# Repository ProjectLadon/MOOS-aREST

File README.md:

# MOOS-paREST
A connector between MOOS and aREST running on Arduino satellite nodes. It provides a direct linkage between aREST endpoints and MOOS variables.

## Dependencies
* MOOS-IvP
* https://github.com/Tencent/rapidjson/ -- provides JSON parse/deparse
* https://curl.haxx.se/libcurl/ -- provides HTTP client interface

## Configuration Options
* interface -- defines the aRest interface to be used, according to the following schema:
```
{
	"$schema": "http://json-schema.org/schema#",
	"id": "AREST_interface",
	"type": "object",
	"properties":{
		"oneOf": [
			{
				"type":"object",
				"properties": {
					"interfaceType": "serial",
					"interface": {
						"type":"string",
						"pattern": "",
						"$comment": "pattern needs to be filled in so it only accepts device names"
					},
					"speed": {"type":"integer", "$comment":"defaults to 115200"},
					"serialFormat": {
						"type":"string",
						"pattern": "",
						"$comment":"Pattern needs to be filled in so it only permits sane values",
						"$comment":"Defaults to 8N1"
					}
				},
				"required":["interfaceType", "interface"],
				"$comment": "This is for a serial interface"
			},
			{
				"type":"object",
				"properties": {
					"interfaceType": "network",
					"url": {"type":"string", "format": "uri"},
				},
				"required":["interfaceType", "url"],
				"$comment": "This is for a network interface"
			}
		]
	}
}
```
* digitalRead -- read a given digital pin and publish the result on MOOSDB as a BINARY, as defined by the following JSON schema:
```
{
	"$schema": "http://json-schema.org/schema#",
	"id": "AREST_digitalRead",
	"type": "object",
	"properties":{
		"function":"digitalRead",
		"pin":{"type":"number"},
		"variable":{
			"type":"string",
			"$comment": "This must be a free variable name; it will be published as a BINARY"
		}
	},
	"required":["function","pin","variable"]
}
```
* digitalWrite -- write from a given MOOSDB BINARY variable to a given digital pin, as defined by the following JSON schema:
```
{
	"$schema": "http://json-schema.org/schema#",
	"id": "AREST_digitalWrite",
	"type": "object",
	"properties":{
		"function":"digitalWrite",
		"pin":{"type":"number"},
		"variable":{
			"type":"string",
			"$comment": "This must be an existing BINARY variable"
		}
	},
	"required":["function","pin","variable"]
}
```
* analogRead -- read a given analog pin and publish the result on MOOSDB as a DOUBLE, as defined by the following JSON schema. Note that the offset value (if present) will be added to the received value and the result will be multiplied by the gain (if present) prior to publication.
```
{
	"$schema": "http://json-schema.org/schema#",
	"id": "AREST_analogRead",
	"type": "object",
	"properties":{
		"function":"analogRead",
		"pin":{"type":"number"},
		"variable":{
			"type":"string",
			"$comment": "This must be a free variable name; it will be published as a DOUBLE"
		},
		"offset":{"type":"integer"},
		"gain":{"type":"number"}
	},
	"required":["function","pin","variable"]
}
```
* analogWrite -- write from a given MOOSDB DOUBLE variable to a given analog pin, as defined by the following JSON schema. Note that the offset value (if present) will be added to the received value and the result will be multiplied by the gain (if present) prior to transmission.
```
{
	"$schema": "http://json-schema.org/schema#",
	"id": "AREST_analogWrite",
	"type": "object",
	"properties":{
		"function":"analogWrite",
		"pin":{"type":"number"},
		"variable":{
			"type":"string",
			"$comment": "This must be an existing DOUBLE variable"
		},
		"offset":{"type":"integer"},
		"gain":{"type":"number"},
		"maxValue":{"type":"integer"},
		"minValue":{"type":"integer"}
	},
	"required":["function","pin","variable"]
}
```
* variable -- read a given variable and publish the result on MOOSDB as a DOUBLE or STRING, as defined by the following JSON schema:
```
{
	"$schema": "http://json-schema.org/schema#",
	"id": "AREST_variable",
	"type": "object",
	"properties":{
		"function":"variable",
		"name":{"type":"string"},
		"variableType":{"type":"string","enum":["STRING","DOUBLE"]},
		"variable":{
			"type":"string",
			"$comment": "This must be a free variable name; it will be published as defined by variableType"
		}
	},
	"required":["function","name","variable","variableType"]
}
```
* function -- activate a given function with (optional) parameters and return the result on a MOOSDB variable. The behavior is defined by JSON with the following schema:
```
{
	"$schema": "http://json-schema.org/schema#",
	"id": "AREST_function",
	"type": "object",
	"properties":{
		"function":"function",
		"name":{"type":"string"},
		"parameters":{
			"type":"array",
			"items":{
				"type": "object",
				"properties": {
					"name": {"type":"string"},
					"inputVariable": {"type":"string"},
					"inputVariableType": {"type": "string", "enum":["DOUBLE", "STRING", "BINARY"]}
				},
				"required":["name", "inputVariable", "inputVariableType"]
			}
		},
		"returnType":{"type":"string","enum":["STRING","DOUBLE"]},
		"returnVariable":{
			"type":"string",
			"$comment": "This must be a free variable name; it will be published as a DOUBLE"
		}
	},
	"required":["function","name"]
}
```
* confFile -- path to a configuration file with any combination of other objects. The contents of the file must be a single JSON array of objects conforming to one or more of the previous schemas.
* digitalPollPeriod -- polling period for digitalRead items, in ticks.
* analogPollPeriod -- polling period for analogRead items, in ticks.
* functionPollPeriod -- polling period for function items, in ticks.
* variablePollPeriod -- polling period for variable items, in ticks.

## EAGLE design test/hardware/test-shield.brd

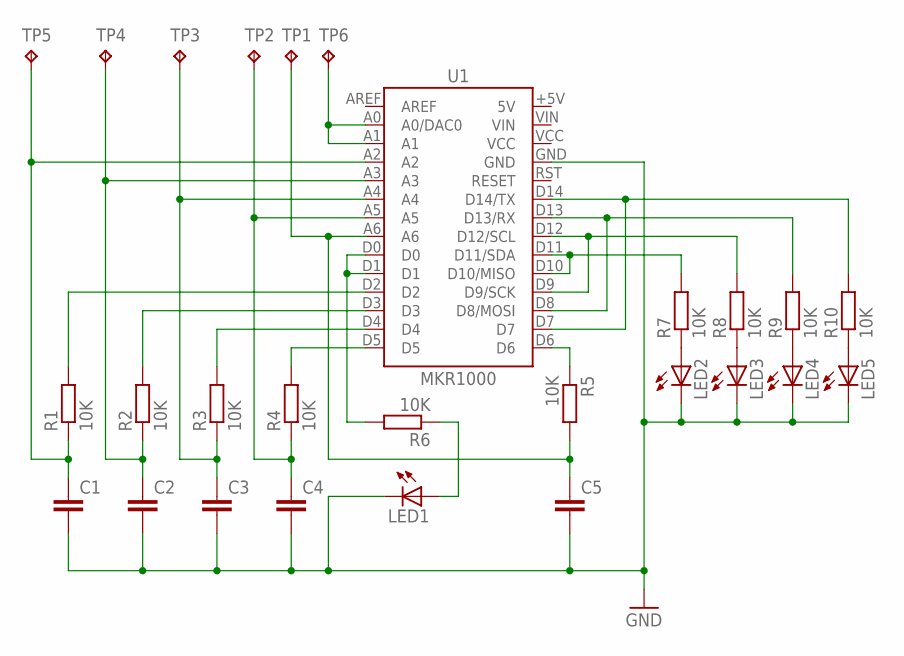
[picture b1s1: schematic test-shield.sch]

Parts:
C1, C2, C3, C4, C5: C-EUC0603; C0603
LED1, LED2, LED3, LED4, LED5: LEDCHIPLED_0805; CHIPLED_0805
R1, R2, R3, R4, R5, R6, R7, R8, R9, R10: 10K; R0603
TP1, TP2, TP3, TP4, TP5, TP6: TPPAD1-13; P1-13
U1: MKR1000; MKR1000-THRU-HOLE

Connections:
GND: C1.2, C2.2, C3.2, C4.2, C5.2, LED1.C, LED2.C, LED3.C, LED4.C, LED5.C, U1.GND
unnamed: R1.2, U1.D2
unnamed: R2.2, U1.D3
unnamed: R3.2, U1.D4
unnamed: R4.2, U1.D5
unnamed: R5.1, U1.D6
unnamed: C1.1, R1.1, TP5.TP, U1.A2
unnamed: C2.1, R2.1, TP4.TP, U1.A3
unnamed: C3.1, R3.1, TP3.TP, U1.A4
unnamed: C4.1, R4.1, TP2.TP, U1.A5
unnamed: R10.2, U1.D7, U1.D14 (D14/TX)
unnamed: C5.1, R5.2, TP1.TP, U1.A6
unnamed: TP6.TP, U1.A0 (A0/DAC0), U1.A1
unnamed: R6.2, U1.D0, U1.D1
unnamed: R9.2, U1.D8 (D8/MOSI), U1.D13 (D13/RX)
unnamed: R8.2, U1.D9 (D9/SCK), U1.D12 (D12/SCL)
unnamed: R7.2, U1.D10 (D10/MISO), U1.D11 (D11/SDA)
unnamed: LED2.A, R7.1
unnamed: LED3.A, R8.1
unnamed: LED4.A, R9.1
unnamed: LED5.A, R10.1
unnamed: LED1.A, R6.1

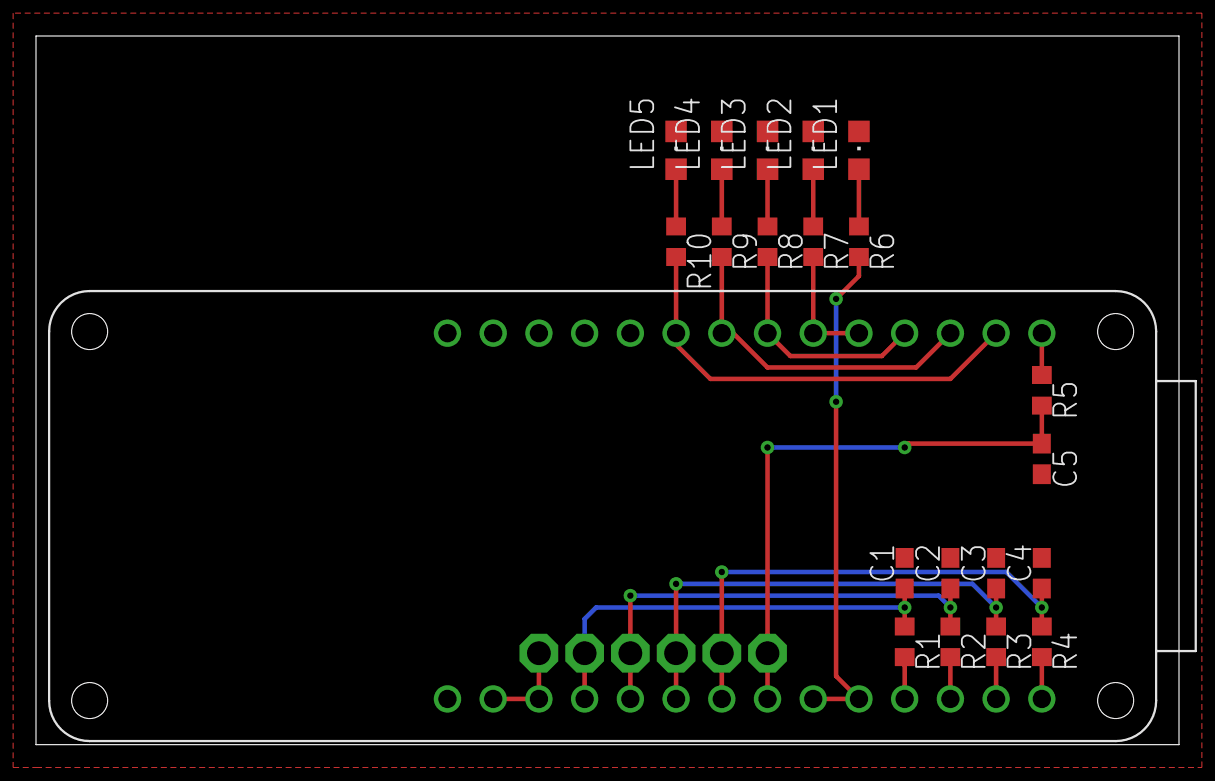
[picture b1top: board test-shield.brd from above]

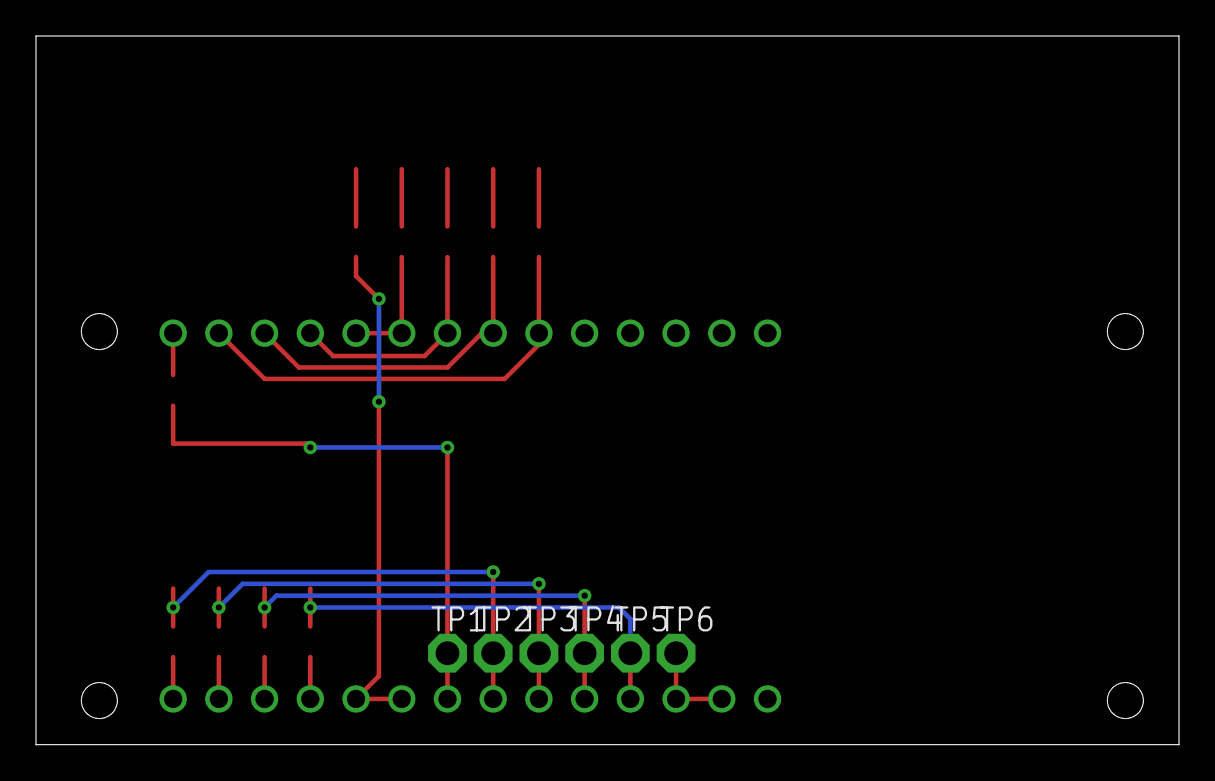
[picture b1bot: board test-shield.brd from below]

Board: 2 copper layers, 63.5 x 39.4 mm, 27 parts (6 on the bottom side), 22 nets.

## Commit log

2017-10-12 Filled in README.md
2017-10-12 Created json schema files, updated json in README.md to fix errors found in schema files.
2017-10-15 Update README.md
    Updating names, adding dependencies.
2017-10-28 Created template app
2017-10-28 README updates
2017-10-28 Starting to hang some code on the bones:
2017-10-30 committing before I make some major changes
2017-10-31 And now cmake does what I want...
2017-10-31 Some documentation updates
2017-10-31 Another day, another few dozen lines
2017-11-04 Updates to confFile line
2017-11-05 Adding proper requirements
2017-11-05 Yet more requirements
2017-11-07 SRDs complete through configuration description
2017-11-07 Added OnStartup() and OnNewMail() requirements
2017-11-08 Finished up the top level requirements
2017-11-16 Getting started on testing requirements
2017-11-19 Added some test requirements
2017-11-24 More requirements..
2017-11-24 Added test shield hardware
2017-11-25 Starting in on software design documentation
2017-11-28 Added a bunch of software design items.
2017-12-01 Finished first pass on SDD
2017-12-02 Published SDD
2017-12-02 Working on adding linkages
2017-12-19 Quick tweak
2018-02-01 Updated to build in tree
2018-02-01 Modified it so it compiles and links correctly now
2018-02-04 Checkpoint during development
2018-02-05 Updating with latest code for help
2018-02-05 Completed restItem.cpp through AnalogWrite
2018-02-07 Everything but the last bit of the Configuration class is now implemented and compiles. Still need tests.
2018-02-09 Feature complete and compiling -- still needs tests
2018-02-10 Fixed minor typo in CMakeLists.txt
2018-06-27 Now appears to be working
2018-08-09 Fixed & uparmored config parsing. Not sure how this ever worked
